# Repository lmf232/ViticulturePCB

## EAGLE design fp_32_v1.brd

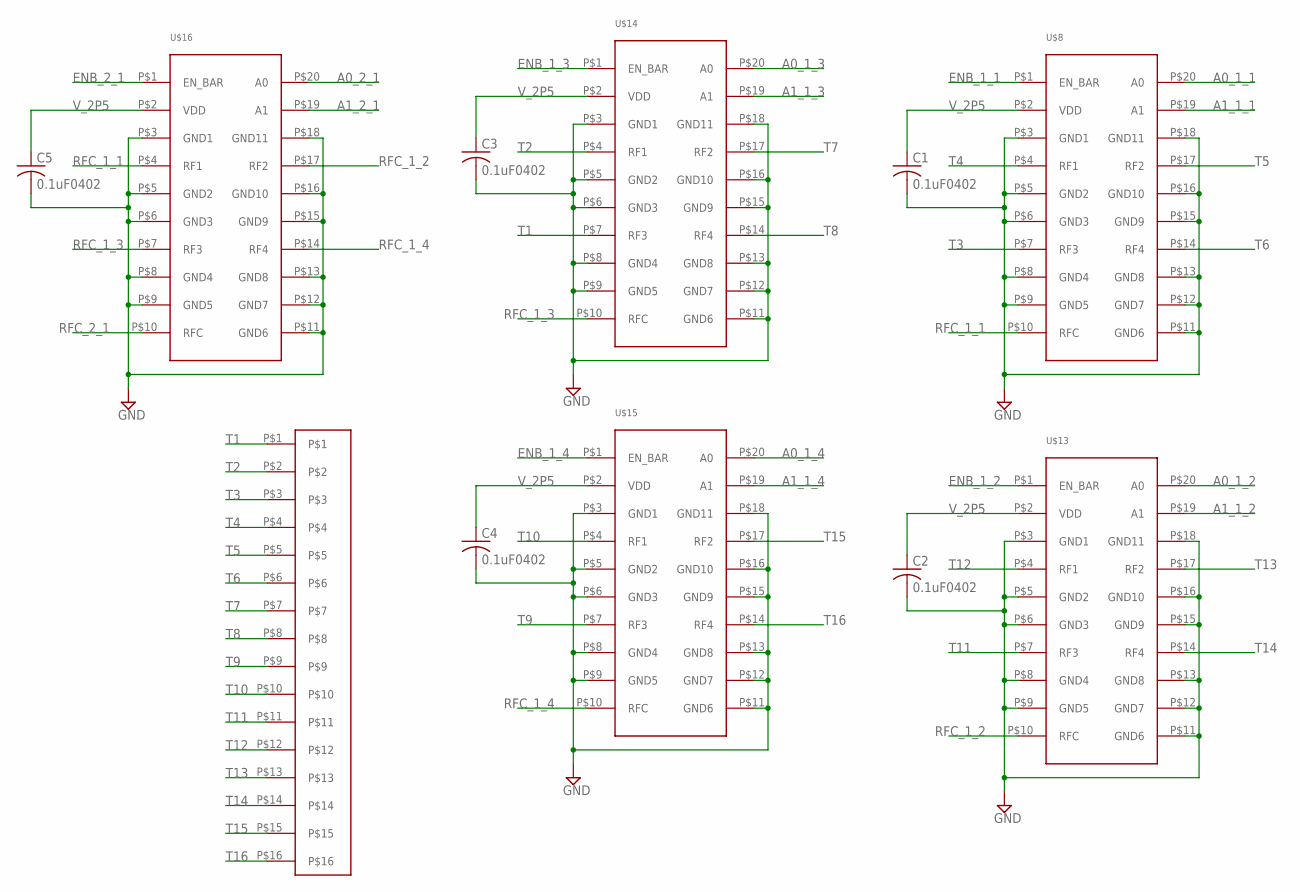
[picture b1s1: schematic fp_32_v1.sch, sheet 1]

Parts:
C1, C2, C3, C4, C5: 0.1uF0402; C0402
U$2: FP-BOND-6MIL; FP_BOND_6MIL
U$8, U$13, U$14, U$15, U$16: TICLIB2_ADG904; TICLIB2_ADG904_TSSOP

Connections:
A0_1_1: U$8.P$20 (A0); also elsewhere on the board
A0_1_2: U$13.P$20 (A0); also elsewhere on the board
A0_1_3: U$14.P$20 (A0); also elsewhere on the board
A0_1_4: U$15.P$20 (A0); also elsewhere on the board
A0_2_1: U$16.P$20 (A0); also elsewhere on the board
A1_1_1: U$8.P$19 (A1); also elsewhere on the board
A1_1_2: U$13.P$19 (A1); also elsewhere on the board
A1_1_3: U$14.P$19 (A1); also elsewhere on the board
A1_1_4: U$15.P$19 (A1); also elsewhere on the board
A1_2_1: U$16.P$19 (A1); also elsewhere on the board
ENB_1_1: U$8.P$1 (EN_BAR); also elsewhere on the board
ENB_1_2: U$13.P$1 (EN_BAR); also elsewhere on the board
ENB_1_3: U$14.P$1 (EN_BAR); also elsewhere on the board
ENB_1_4: U$15.P$1 (EN_BAR); also elsewhere on the board
ENB_2_1: U$16.P$1 (EN_BAR); also elsewhere on the board
GND: C1.2, C2.2, C3.2, C4.2, C5.2, U$8.P$3 (GND1), U$8.P$5 (GND2), U$8.P$6 (GND3), U$8.P$8 (GND4), U$8.P$9 (GND5), U$8.P$11 (GND6), U$8.P$12 (GND7), U$8.P$13 (GND8), U$8.P$15 (GND9), U$8.P$16 (GND10), U$8.P$18 (GND11), U$13.P$3 (GND1), U$13.P$5 (GND2), U$13.P$6 (GND3), U$13.P$8 (GND4), U$13.P$9 (GND5), U$13.P$11 (GND6), U$13.P$12 (GND7), U$13.P$13 (GND8), U$13.P$15 (GND9), U$13.P$16 (GND10), U$13.P$18 (GND11), U$14.P$3 (GND1), U$14.P$5 (GND2), U$14.P$6 (GND3), U$14.P$8 (GND4), U$14.P$9 (GND5), U$14.P$11 (GND6), U$14.P$12 (GND7), U$14.P$13 (GND8), U$14.P$15 (GND9), U$14.P$16 (GND10), U$14.P$18 (GND11), U$15.P$3 (GND1), U$15.P$5 (GND2), U$15.P$6 (GND3), U$15.P$8 (GND4), U$15.P$9 (GND5), U$15.P$11 (GND6), U$15.P$12 (GND7), U$15.P$13 (GND8), U$15.P$15 (GND9), U$15.P$16 (GND10), U$15.P$18 (GND11), U$16.P$3 (GND1), U$16.P$5 (GND2), U$16.P$6 (GND3), U$16.P$8 (GND4), U$16.P$9 (GND5), U$16.P$11 (GND6), U$16.P$12 (GND7), U$16.P$13 (GND8), U$16.P$15 (GND9), U$16.P$16 (GND10), U$16.P$18 (GND11); also elsewhere on the board
RFC_1_1: U$8.P$10 (RFC), U$16.P$4 (RF1)
RFC_1_2: U$13.P$10 (RFC), U$16.P$17 (RF2)
RFC_1_3: U$14.P$10 (RFC), U$16.P$7 (RF3)
RFC_1_4: U$15.P$10 (RFC), U$16.P$14 (RF4)
RFC_2_1: U$16.P$10 (RFC); also elsewhere on the board
T1: U$2.P$1, U$14.P$7 (RF3)
T2: U$2.P$2, U$14.P$4 (RF1)
T3: U$2.P$3, U$8.P$7 (RF3)
T4: U$2.P$4, U$8.P$4 (RF1)
T5: U$2.P$5, U$8.P$17 (RF2)
T6: U$2.P$6, U$8.P$14 (RF4)
T7: U$2.P$7, U$14.P$17 (RF2)
T8: U$2.P$8, U$14.P$14 (RF4)
T9: U$2.P$9, U$15.P$7 (RF3)
T10: U$2.P$10, U$15.P$4 (RF1)
T11: U$2.P$11, U$13.P$7 (RF3)
T12: U$2.P$12, U$13.P$4 (RF1)
T13: U$2.P$13, U$13.P$17 (RF2)
T14: U$2.P$14, U$13.P$14 (RF4)
T15: U$2.P$15, U$15.P$17 (RF2)
T16: U$2.P$16, U$15.P$14 (RF4)
V_2P5: C1.1, C2.1, C3.1, C4.1, C5.1, U$8.P$2 (VDD), U$13.P$2 (VDD), U$14.P$2 (VDD), U$15.P$2 (VDD), U$16.P$2 (VDD); also elsewhere on the board

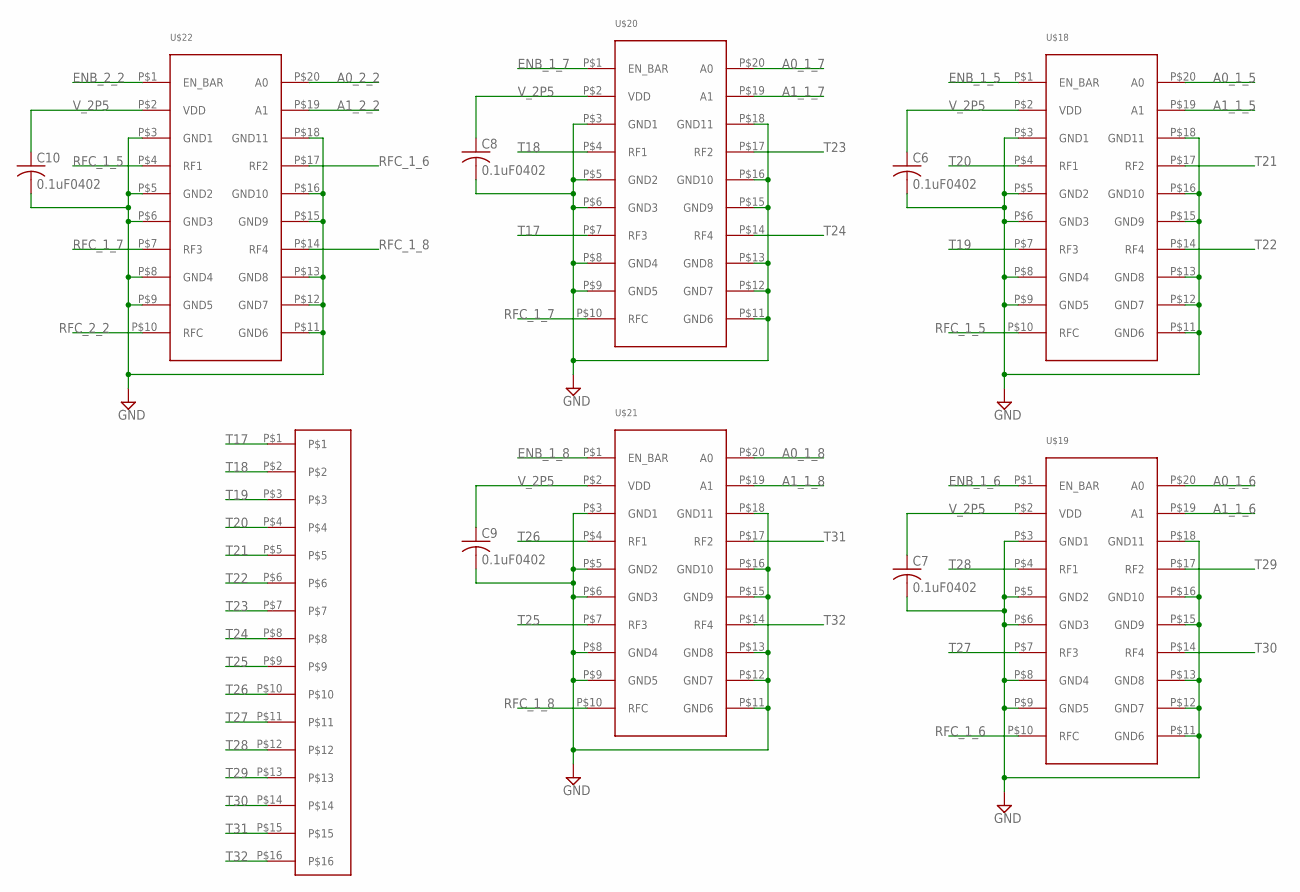
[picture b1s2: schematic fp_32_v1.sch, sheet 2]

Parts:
C6, C7, C8, C9, C10: 0.1uF0402; C0402
U$17: FP-BOND-6MIL; FP_BOND_6MIL
U$18, U$19, U$20, U$21, U$22: TICLIB2_ADG904; TICLIB2_ADG904_TSSOP

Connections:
A0_1_5: U$18.P$20 (A0); also elsewhere on the board
A0_1_6: U$19.P$20 (A0); also elsewhere on the board
A0_1_7: U$20.P$20 (A0); also elsewhere on the board
A0_1_8: U$21.P$20 (A0); also elsewhere on the board
A0_2_2: U$22.P$20 (A0); also elsewhere on the board
A1_1_5: U$18.P$19 (A1); also elsewhere on the board
A1_1_6: U$19.P$19 (A1); also elsewhere on the board
A1_1_7: U$20.P$19 (A1); also elsewhere on the board
A1_1_8: U$21.P$19 (A1); also elsewhere on the board
A1_2_2: U$22.P$19 (A1); also elsewhere on the board
ENB_1_5: U$18.P$1 (EN_BAR); also elsewhere on the board
ENB_1_6: U$19.P$1 (EN_BAR); also elsewhere on the board
ENB_1_7: U$20.P$1 (EN_BAR); also elsewhere on the board
ENB_1_8: U$21.P$1 (EN_BAR); also elsewhere on the board
ENB_2_2: U$22.P$1 (EN_BAR); also elsewhere on the board
GND: C6.2, C7.2, C8.2, C9.2, C10.2, U$18.P$3 (GND1), U$18.P$5 (GND2), U$18.P$6 (GND3), U$18.P$8 (GND4), U$18.P$9 (GND5), U$18.P$11 (GND6), U$18.P$12 (GND7), U$18.P$13 (GND8), U$18.P$15 (GND9), U$18.P$16 (GND10), U$18.P$18 (GND11), U$19.P$3 (GND1), U$19.P$5 (GND2), U$19.P$6 (GND3), U$19.P$8 (GND4), U$19.P$9 (GND5), U$19.P$11 (GND6), U$19.P$12 (GND7), U$19.P$13 (GND8), U$19.P$15 (GND9), U$19.P$16 (GND10), U$19.P$18 (GND11), U$20.P$3 (GND1), U$20.P$5 (GND2), U$20.P$6 (GND3), U$20.P$8 (GND4), U$20.P$9 (GND5), U$20.P$11 (GND6), U$20.P$12 (GND7), U$20.P$13 (GND8), U$20.P$15 (GND9), U$20.P$16 (GND10), U$20.P$18 (GND11), U$21.P$3 (GND1), U$21.P$5 (GND2), U$21.P$6 (GND3), U$21.P$8 (GND4), U$21.P$9 (GND5), U$21.P$11 (GND6), U$21.P$12 (GND7), U$21.P$13 (GND8), U$21.P$15 (GND9), U$21.P$16 (GND10), U$21.P$18 (GND11), U$22.P$3 (GND1), U$22.P$5 (GND2), U$22.P$6 (GND3), U$22.P$8 (GND4), U$22.P$9 (GND5), U$22.P$11 (GND6), U$22.P$12 (GND7), U$22.P$13 (GND8), U$22.P$15 (GND9), U$22.P$16 (GND10), U$22.P$18 (GND11); also elsewhere on the board
RFC_1_5: U$18.P$10 (RFC), U$22.P$4 (RF1)
RFC_1_6: U$19.P$10 (RFC), U$22.P$17 (RF2)
RFC_1_7: U$20.P$10 (RFC), U$22.P$7 (RF3)
RFC_1_8: U$21.P$10 (RFC), U$22.P$14 (RF4)
RFC_2_2: U$22.P$10 (RFC); also elsewhere on the board
T17: U$17.P$1, U$20.P$7 (RF3)
T18: U$17.P$2, U$20.P$4 (RF1)
T19: U$17.P$3, U$18.P$7 (RF3)
T20: U$17.P$4, U$18.P$4 (RF1)
T21: U$17.P$5, U$18.P$17 (RF2)
T22: U$17.P$6, U$18.P$14 (RF4)
T23: U$17.P$7, U$20.P$17 (RF2)
T24: U$17.P$8, U$20.P$14 (RF4)
T25: U$17.P$9, U$21.P$7 (RF3)
T26: U$17.P$10, U$21.P$4 (RF1)
T27: U$17.P$11, U$19.P$7 (RF3)
T28: U$17.P$12, U$19.P$4 (RF1)
T29: U$17.P$13, U$19.P$17 (RF2)
T30: U$17.P$14, U$19.P$14 (RF4)
T31: U$17.P$15, U$21.P$17 (RF2)
T32: U$17.P$16, U$21.P$14 (RF4)
V_2P5: C6.1, C7.1, C8.1, C9.1, C10.1, U$18.P$2 (VDD), U$19.P$2 (VDD), U$20.P$2 (VDD), U$21.P$2 (VDD), U$22.P$2 (VDD); also elsewhere on the board

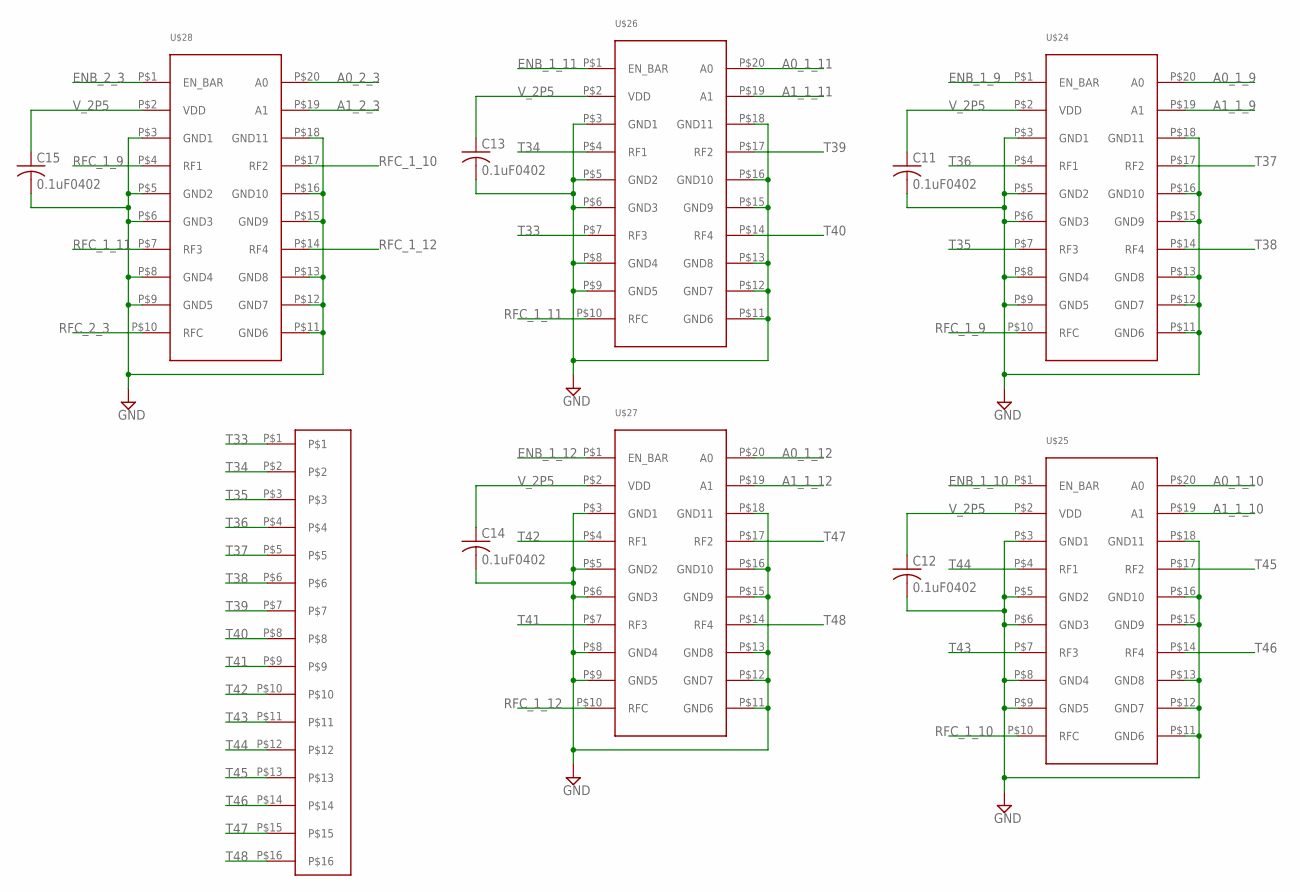
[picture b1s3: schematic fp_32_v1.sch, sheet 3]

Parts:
C11, C12, C13, C14, C15: 0.1uF0402; C0402
U$23: FP-BOND-6MIL; FP_BOND_6MIL
U$24, U$25, U$26, U$27, U$28: TICLIB2_ADG904; TICLIB2_ADG904_TSSOP

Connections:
A0_1_9: U$24.P$20 (A0); also elsewhere on the board
A0_1_10: U$25.P$20 (A0); also elsewhere on the board
A0_1_11: U$26.P$20 (A0); also elsewhere on the board
A0_1_12: U$27.P$20 (A0); also elsewhere on the board
A0_2_3: U$28.P$20 (A0); also elsewhere on the board
A1_1_9: U$24.P$19 (A1); also elsewhere on the board
A1_1_10: U$25.P$19 (A1); also elsewhere on the board
A1_1_11: U$26.P$19 (A1); also elsewhere on the board
A1_1_12: U$27.P$19 (A1); also elsewhere on the board
A1_2_3: U$28.P$19 (A1); also elsewhere on the board
ENB_1_9: U$24.P$1 (EN_BAR); also elsewhere on the board
ENB_1_10: U$25.P$1 (EN_BAR); also elsewhere on the board
ENB_1_11: U$26.P$1 (EN_BAR); also elsewhere on the board
ENB_1_12: U$27.P$1 (EN_BAR); also elsewhere on the board
ENB_2_3: U$28.P$1 (EN_BAR); also elsewhere on the board
GND: C11.2, C12.2, C13.2, C14.2, C15.2, U$24.P$3 (GND1), U$24.P$5 (GND2), U$24.P$6 (GND3), U$24.P$8 (GND4), U$24.P$9 (GND5), U$24.P$11 (GND6), U$24.P$12 (GND7), U$24.P$13 (GND8), U$24.P$15 (GND9), U$24.P$16 (GND10), U$24.P$18 (GND11), U$25.P$3 (GND1), U$25.P$5 (GND2), U$25.P$6 (GND3), U$25.P$8 (GND4), U$25.P$9 (GND5), U$25.P$11 (GND6), U$25.P$12 (GND7), U$25.P$13 (GND8), U$25.P$15 (GND9), U$25.P$16 (GND10), U$25.P$18 (GND11), U$26.P$3 (GND1), U$26.P$5 (GND2), U$26.P$6 (GND3), U$26.P$8 (GND4), U$26.P$9 (GND5), U$26.P$11 (GND6), U$26.P$12 (GND7), U$26.P$13 (GND8), U$26.P$15 (GND9), U$26.P$16 (GND10), U$26.P$18 (GND11), U$27.P$3 (GND1), U$27.P$5 (GND2), U$27.P$6 (GND3), U$27.P$8 (GND4), U$27.P$9 (GND5), U$27.P$11 (GND6), U$27.P$12 (GND7), U$27.P$13 (GND8), U$27.P$15 (GND9), U$27.P$16 (GND10), U$27.P$18 (GND11), U$28.P$3 (GND1), U$28.P$5 (GND2), U$28.P$6 (GND3), U$28.P$8 (GND4), U$28.P$9 (GND5), U$28.P$11 (GND6), U$28.P$12 (GND7), U$28.P$13 (GND8), U$28.P$15 (GND9), U$28.P$16 (GND10), U$28.P$18 (GND11); also elsewhere on the board
RFC_1_9: U$24.P$10 (RFC), U$28.P$4 (RF1)
RFC_1_10: U$25.P$10 (RFC), U$28.P$17 (RF2)
RFC_1_11: U$26.P$10 (RFC), U$28.P$7 (RF3)
RFC_1_12: U$27.P$10 (RFC), U$28.P$14 (RF4)
RFC_2_3: U$28.P$10 (RFC); also elsewhere on the board
T33: U$23.P$1, U$26.P$7 (RF3)
T34: U$23.P$2, U$26.P$4 (RF1)
T35: U$23.P$3, U$24.P$7 (RF3)
T36: U$23.P$4, U$24.P$4 (RF1)
T37: U$23.P$5, U$24.P$17 (RF2)
T38: U$23.P$6, U$24.P$14 (RF4)
T39: U$23.P$7, U$26.P$17 (RF2)
T40: U$23.P$8, U$26.P$14 (RF4)
T41: U$23.P$9, U$27.P$7 (RF3)
T42: U$23.P$10, U$27.P$4 (RF1)
T43: U$23.P$11, U$25.P$7 (RF3)
T44: U$23.P$12, U$25.P$4 (RF1)
T45: U$23.P$13, U$25.P$17 (RF2)
T46: U$23.P$14, U$25.P$14 (RF4)
T47: U$23.P$15, U$27.P$17 (RF2)
T48: U$23.P$16, U$27.P$14 (RF4)
V_2P5: C11.1, C12.1, C13.1, C14.1, C15.1, U$24.P$2 (VDD), U$25.P$2 (VDD), U$26.P$2 (VDD), U$27.P$2 (VDD), U$28.P$2 (VDD); also elsewhere on the board

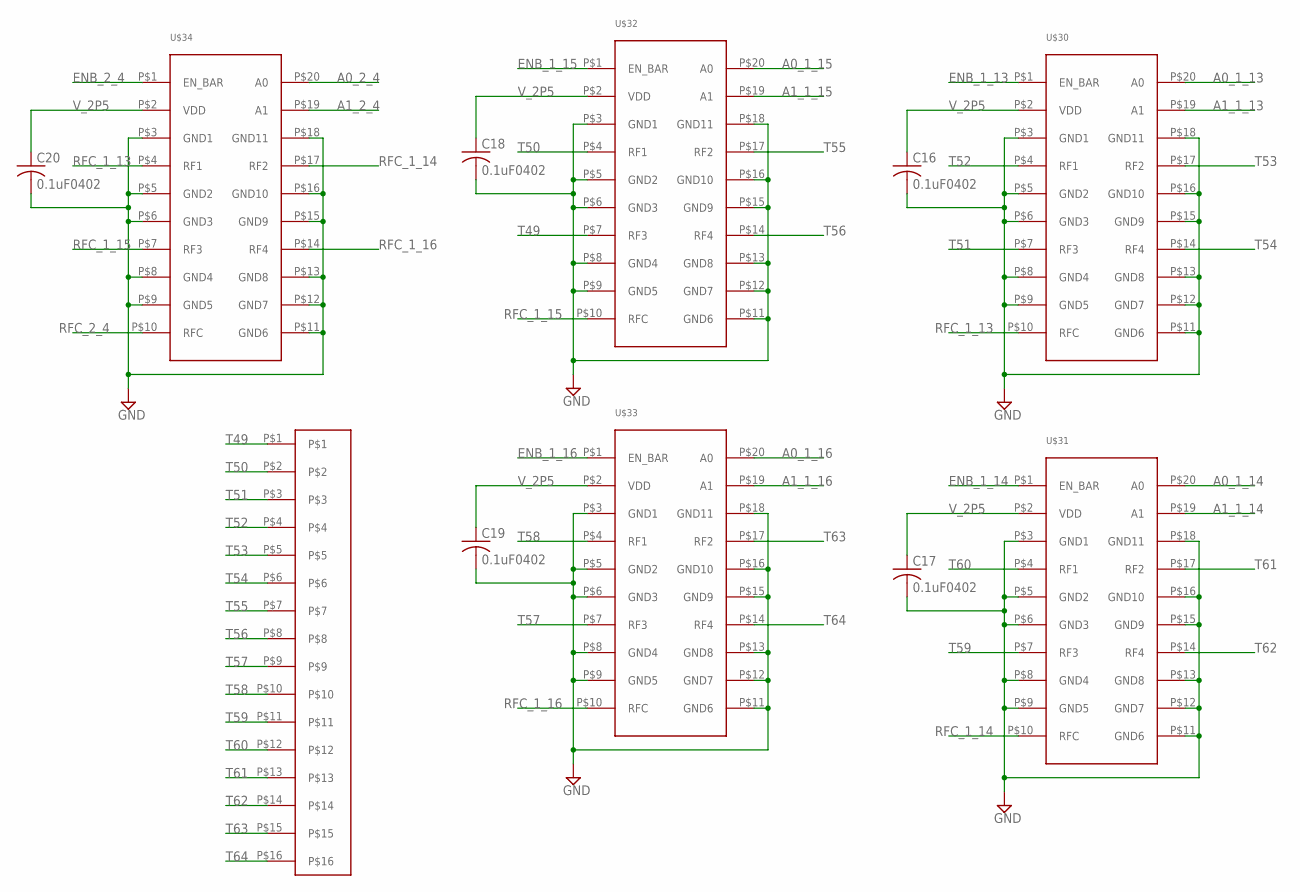
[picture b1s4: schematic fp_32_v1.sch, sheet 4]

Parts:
C16, C17, C18, C19, C20: 0.1uF0402; C0402
U$29: FP-BOND-6MIL; FP_BOND_6MIL
U$30, U$31, U$32, U$33, U$34: TICLIB2_ADG904; TICLIB2_ADG904_TSSOP

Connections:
A0_1_13: U$30.P$20 (A0); also elsewhere on the board
A0_1_14: U$31.P$20 (A0); also elsewhere on the board
A0_1_15: U$32.P$20 (A0); also elsewhere on the board
A0_1_16: U$33.P$20 (A0); also elsewhere on the board
A0_2_4: U$34.P$20 (A0); also elsewhere on the board
A1_1_13: U$30.P$19 (A1); also elsewhere on the board
A1_1_14: U$31.P$19 (A1); also elsewhere on the board
A1_1_15: U$32.P$19 (A1); also elsewhere on the board
A1_1_16: U$33.P$19 (A1); also elsewhere on the board
A1_2_4: U$34.P$19 (A1); also elsewhere on the board
ENB_1_13: U$30.P$1 (EN_BAR); also elsewhere on the board
ENB_1_14: U$31.P$1 (EN_BAR); also elsewhere on the board
ENB_1_15: U$32.P$1 (EN_BAR); also elsewhere on the board
ENB_1_16: U$33.P$1 (EN_BAR); also elsewhere on the board
ENB_2_4: U$34.P$1 (EN_BAR); also elsewhere on the board
GND: C16.2, C17.2, C18.2, C19.2, C20.2, U$30.P$3 (GND1), U$30.P$5 (GND2), U$30.P$6 (GND3), U$30.P$8 (GND4), U$30.P$9 (GND5), U$30.P$11 (GND6), U$30.P$12 (GND7), U$30.P$13 (GND8), U$30.P$15 (GND9), U$30.P$16 (GND10), U$30.P$18 (GND11), U$31.P$3 (GND1), U$31.P$5 (GND2), U$31.P$6 (GND3), U$31.P$8 (GND4), U$31.P$9 (GND5), U$31.P$11 (GND6), U$31.P$12 (GND7), U$31.P$13 (GND8), U$31.P$15 (GND9), U$31.P$16 (GND10), U$31.P$18 (GND11), U$32.P$3 (GND1), U$32.P$5 (GND2), U$32.P$6 (GND3), U$32.P$8 (GND4), U$32.P$9 (GND5), U$32.P$11 (GND6), U$32.P$12 (GND7), U$32.P$13 (GND8), U$32.P$15 (GND9), U$32.P$16 (GND10), U$32.P$18 (GND11), U$33.P$3 (GND1), U$33.P$5 (GND2), U$33.P$6 (GND3), U$33.P$8 (GND4), U$33.P$9 (GND5), U$33.P$11 (GND6), U$33.P$12 (GND7), U$33.P$13 (GND8), U$33.P$15 (GND9), U$33.P$16 (GND10), U$33.P$18 (GND11), U$34.P$3 (GND1), U$34.P$5 (GND2), U$34.P$6 (GND3), U$34.P$8 (GND4), U$34.P$9 (GND5), U$34.P$11 (GND6), U$34.P$12 (GND7), U$34.P$13 (GND8), U$34.P$15 (GND9), U$34.P$16 (GND10), U$34.P$18 (GND11); also elsewhere on the board
RFC_1_13: U$30.P$10 (RFC), U$34.P$4 (RF1)
RFC_1_14: U$31.P$10 (RFC), U$34.P$17 (RF2)
RFC_1_15: U$32.P$10 (RFC), U$34.P$7 (RF3)
RFC_1_16: U$33.P$10 (RFC), U$34.P$14 (RF4)
RFC_2_4: U$34.P$10 (RFC); also elsewhere on the board
T49: U$29.P$1, U$32.P$7 (RF3)
T50: U$29.P$2, U$32.P$4 (RF1)
T51: U$29.P$3, U$30.P$7 (RF3)
T52: U$29.P$4, U$30.P$4 (RF1)
T53: U$29.P$5, U$30.P$17 (RF2)
T54: U$29.P$6, U$30.P$14 (RF4)
T55: U$29.P$7, U$32.P$17 (RF2)
T56: U$29.P$8, U$32.P$14 (RF4)
T57: U$29.P$9, U$33.P$7 (RF3)
T58: U$29.P$10, U$33.P$4 (RF1)
T59: U$29.P$11, U$31.P$7 (RF3)
T60: U$29.P$12, U$31.P$4 (RF1)
T61: U$29.P$13, U$31.P$17 (RF2)
T62: U$29.P$14, U$31.P$14 (RF4)
T63: U$29.P$15, U$33.P$17 (RF2)
T64: U$29.P$16, U$33.P$14 (RF4)
V_2P5: C16.1, C17.1, C18.1, C19.1, C20.1, U$30.P$2 (VDD), U$31.P$2 (VDD), U$32.P$2 (VDD), U$33.P$2 (VDD), U$34.P$2 (VDD); also elsewhere on the board

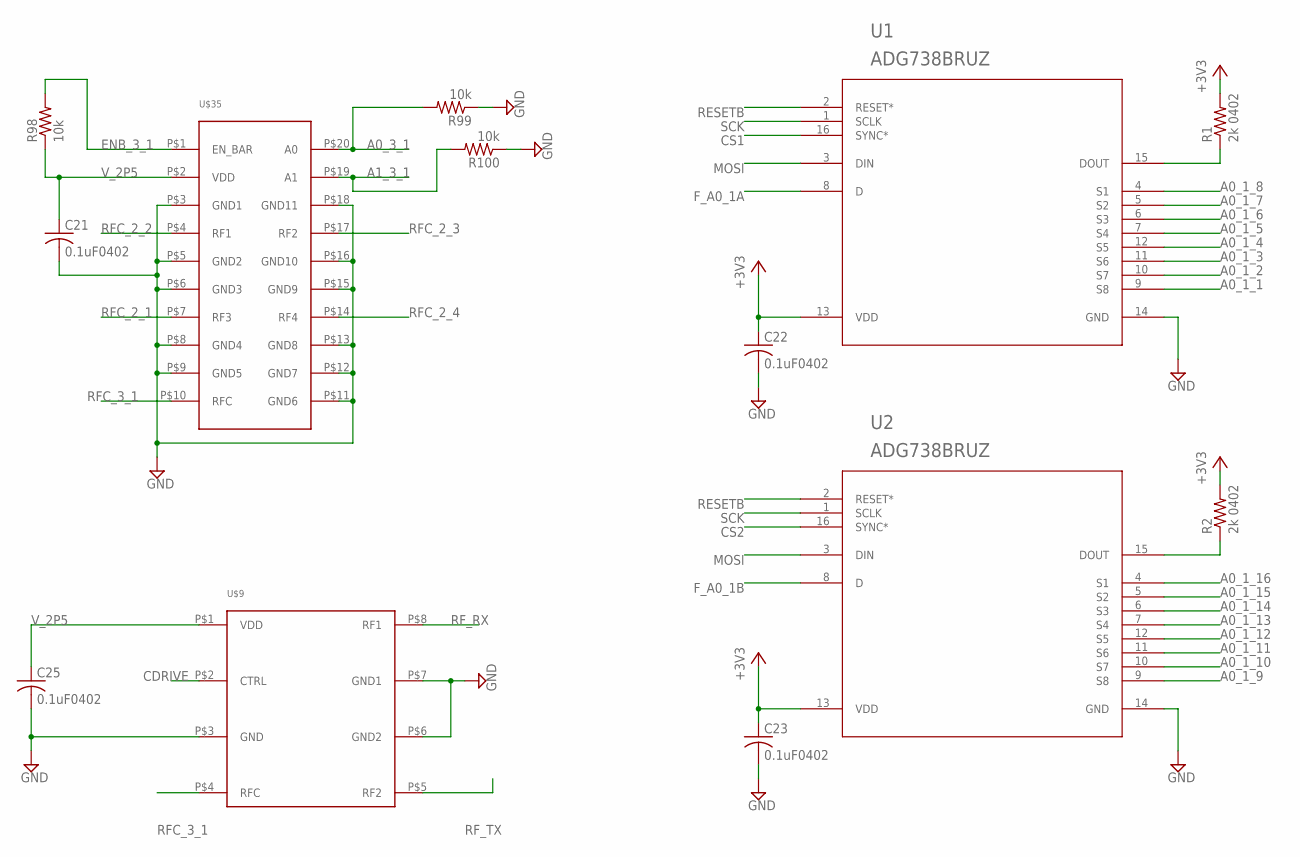
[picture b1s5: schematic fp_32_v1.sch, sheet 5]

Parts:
C21, C22, C23, C25: 0.1uF0402; C0402
R1, R2: 2k 0402; R0402
R98, R99, R100: 10k; R0402
U1, U2: ADG738BRUZ; RU_16
U$9: TIC_TESTING_ADG918BRMZ-500RL7CT; TIC_TESTING_ADG918BRMZ-500RL7CT-ND
U$35: TICLIB2_ADG904; TICLIB2_ADG904_TSSOP

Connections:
+3V3: C22.1, C23.1, R1.2, R2.2, U1.13 (VDD), U2.13 (VDD); also elsewhere on the board
A0_1_1: U1.9 (S8); also elsewhere on the board
A0_1_2: U1.10 (S7); also elsewhere on the board
A0_1_3: U1.11 (S6); also elsewhere on the board
A0_1_4: U1.12 (S5); also elsewhere on the board
A0_1_5: U1.7 (S4); also elsewhere on the board
A0_1_6: U1.6 (S3); also elsewhere on the board
A0_1_7: U1.5 (S2); also elsewhere on the board
A0_1_8: U1.4 (S1); also elsewhere on the board
A0_1_9: U2.9 (S8); also elsewhere on the board
A0_1_10: U2.10 (S7); also elsewhere on the board
A0_1_11: U2.11 (S6); also elsewhere on the board
A0_1_12: U2.12 (S5); also elsewhere on the board
A0_1_13: U2.7 (S4); also elsewhere on the board
A0_1_14: U2.6 (S3); also elsewhere on the board
A0_1_15: U2.5 (S2); also elsewhere on the board
A0_1_16: U2.4 (S1); also elsewhere on the board
A0_3_1: R99.2, U$35.P$20 (A0); also elsewhere on the board
A1_3_1: R100.2, U$35.P$19 (A1); also elsewhere on the board
CDRIVE: U$9.P$2 (CTRL); also elsewhere on the board
CS1: U1.16 (SYNC*); also elsewhere on the board
CS2: U2.16 (SYNC*); also elsewhere on the board
ENB_3_1: R98.2, U$35.P$1 (EN_BAR); also elsewhere on the board
F_A0_1A: U1.8 (D); also elsewhere on the board
F_A0_1B: U2.8 (D); also elsewhere on the board
GND: C21.2, C22.2, C23.2, C25.2, R99.1, R100.1, U1.14 (GND), U2.14 (GND), U$9.P$3 (GND), U$9.P$6 (GND2), U$9.P$7 (GND1), U$35.P$3 (GND1), U$35.P$5 (GND2), U$35.P$6 (GND3), U$35.P$8 (GND4), U$35.P$9 (GND5), U$35.P$11 (GND6), U$35.P$12 (GND7), U$35.P$13 (GND8), U$35.P$15 (GND9), U$35.P$16 (GND10), U$35.P$18 (GND11); also elsewhere on the board
MOSI: U1.3 (DIN), U2.3 (DIN); also elsewhere on the board
unnamed: R1.1, U1.15 (DOUT)
unnamed: R2.1, U2.15 (DOUT)
RESETB: U1.2 (RESET*), U2.2 (RESET*); also elsewhere on the board
RFC_2_1: U$35.P$7 (RF3); also elsewhere on the board
RFC_2_2: U$35.P$4 (RF1); also elsewhere on the board
RFC_2_3: U$35.P$17 (RF2); also elsewhere on the board
RFC_2_4: U$35.P$14 (RF4); also elsewhere on the board
RFC_3_1: U$9.P$4 (RFC), U$35.P$10 (RFC)
RF_RX: U$9.P$8 (RF1); also elsewhere on the board
RF_TX: U$9.P$5 (RF2); also elsewhere on the board
SCK: U1.1 (SCLK), U2.1 (SCLK); also elsewhere on the board
V_2P5: C21.1, C25.1, R98.1, U$9.P$1 (VDD), U$35.P$2 (VDD); also elsewhere on the board

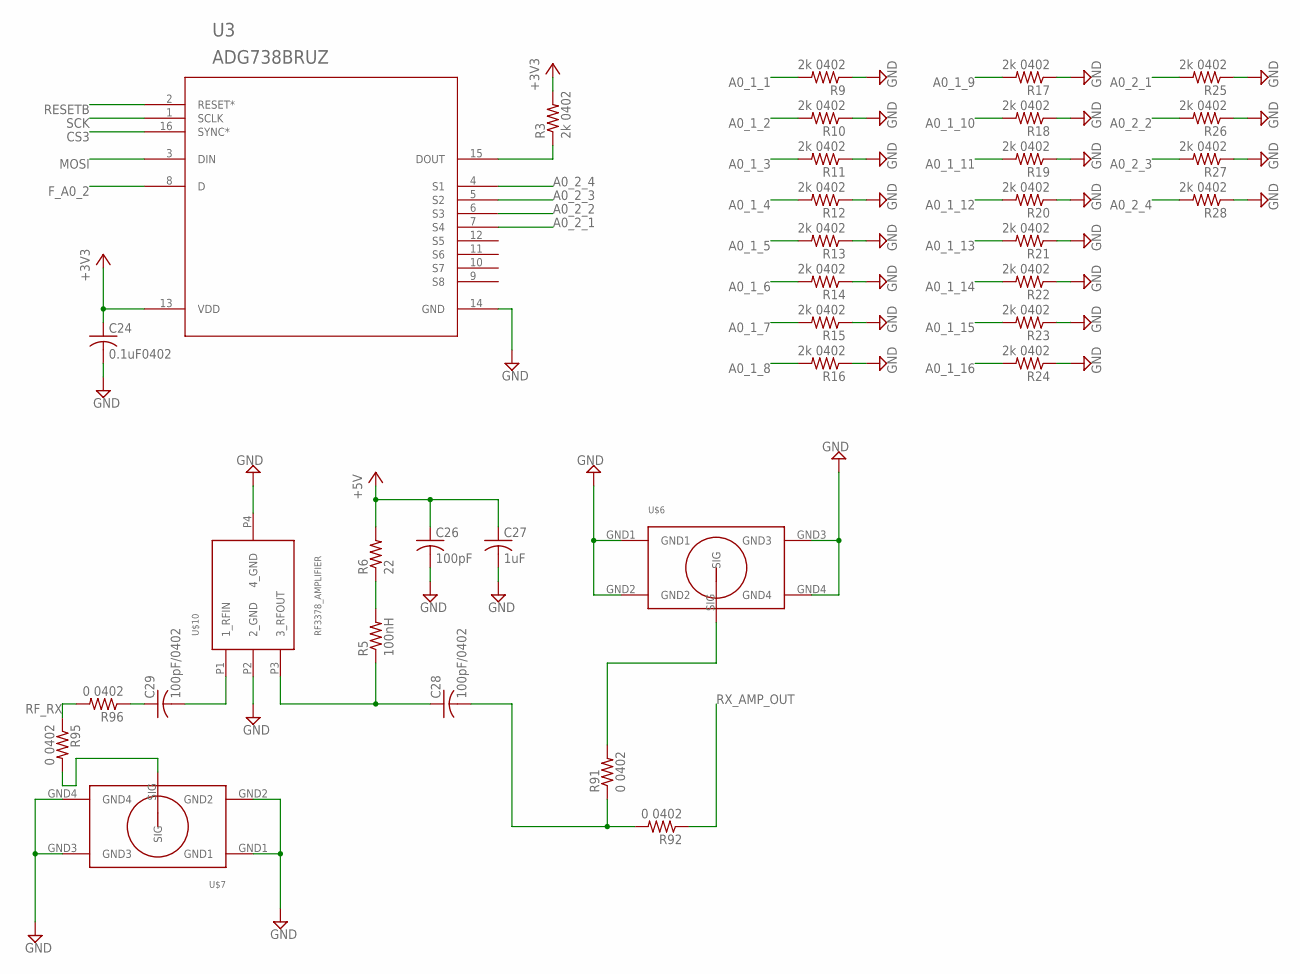
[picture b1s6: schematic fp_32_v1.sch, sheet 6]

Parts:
C24: 0.1uF0402; C0402
C26: 100pF; C0603
C27: 1uF; C0603
C28, C29: 100pF/0402; C0402
R3, R9, R10, R11, R12, R13, R14, R15, R16, R17, R18, R19, R20, R21, R22, R23, R24, R25, R26, R27, R28: 2k 0402; R0402
R5: 100nH; R0603
R6: 22; R0805
R91, R92, R95, R96: 0 0402; R0402
U3: ADG738BRUZ; RU_16
U$6, U$7: MINISMP_PE44970_THRUHOLE; MINISMP_PE44970_THRU_HOLE
U$10: RF3378_AMPLIFIER; TO243AA/SOT89

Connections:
+3V3: C24.1, R3.2, U3.13 (VDD); also elsewhere on the board
+5V: C26.1, C27.1, R6.2; also elsewhere on the board
A0_1_1: R9.2; also elsewhere on the board
A0_1_2: R10.2; also elsewhere on the board
A0_1_3: R11.2; also elsewhere on the board
A0_1_4: R12.2; also elsewhere on the board
A0_1_5: R13.2; also elsewhere on the board
A0_1_6: R14.2; also elsewhere on the board
A0_1_7: R15.2; also elsewhere on the board
A0_1_8: R16.2; also elsewhere on the board
A0_1_9: R17.2; also elsewhere on the board
A0_1_10: R18.2; also elsewhere on the board
A0_1_11: R19.2; also elsewhere on the board
A0_1_12: R20.2; also elsewhere on the board
A0_1_13: R21.2; also elsewhere on the board
A0_1_14: R22.2; also elsewhere on the board
A0_1_15: R23.2; also elsewhere on the board
A0_1_16: R24.2; also elsewhere on the board
A0_2_1: R25.2, U3.7 (S4); also elsewhere on the board
A0_2_2: R26.2, U3.6 (S3); also elsewhere on the board
A0_2_3: R27.2, U3.5 (S2); also elsewhere on the board
A0_2_4: R28.2, U3.4 (S1); also elsewhere on the board
CS3: U3.16 (SYNC*); also elsewhere on the board
F_A0_2: U3.8 (D); also elsewhere on the board
GND: C24.2, C26.2, C27.2, R9.1, R10.1, R11.1, R12.1, R13.1, R14.1, R15.1, R16.1, R17.1, R18.1, R19.1, R20.1, R21.1, R22.1, R23.1, R24.1, R25.1, R26.1, R27.1, R28.1, U3.14 (GND), U$6.GND1, U$6.GND2, U$6.GND3, U$6.GND4, U$7.GND1, U$7.GND2, U$7.GND3, U$7.GND4, U$10.P2 (2_GND), U$10.P4 (4_GND); also elsewhere on the board
MOSI: U3.3 (DIN); also elsewhere on the board
unnamed: R3.1, U3.15 (DOUT)
unnamed: C28.1, R5.1, U$10.P3 (3_RFOUT)
unnamed: R5.2, R6.1
unnamed: C29.2, U$10.P1 (1_RFIN)
unnamed: C28.2, R91.1, R92.2
unnamed: R91.2, U$6.SIG
unnamed: R95.2, U$7.SIG
unnamed: C29.1, R96.1
RESETB: U3.2 (RESET*); also elsewhere on the board
RF_RX: R95.1, R96.2; also elsewhere on the board
RX_AMP_OUT: R92.1; also elsewhere on the board
SCK: U3.1 (SCLK); also elsewhere on the board

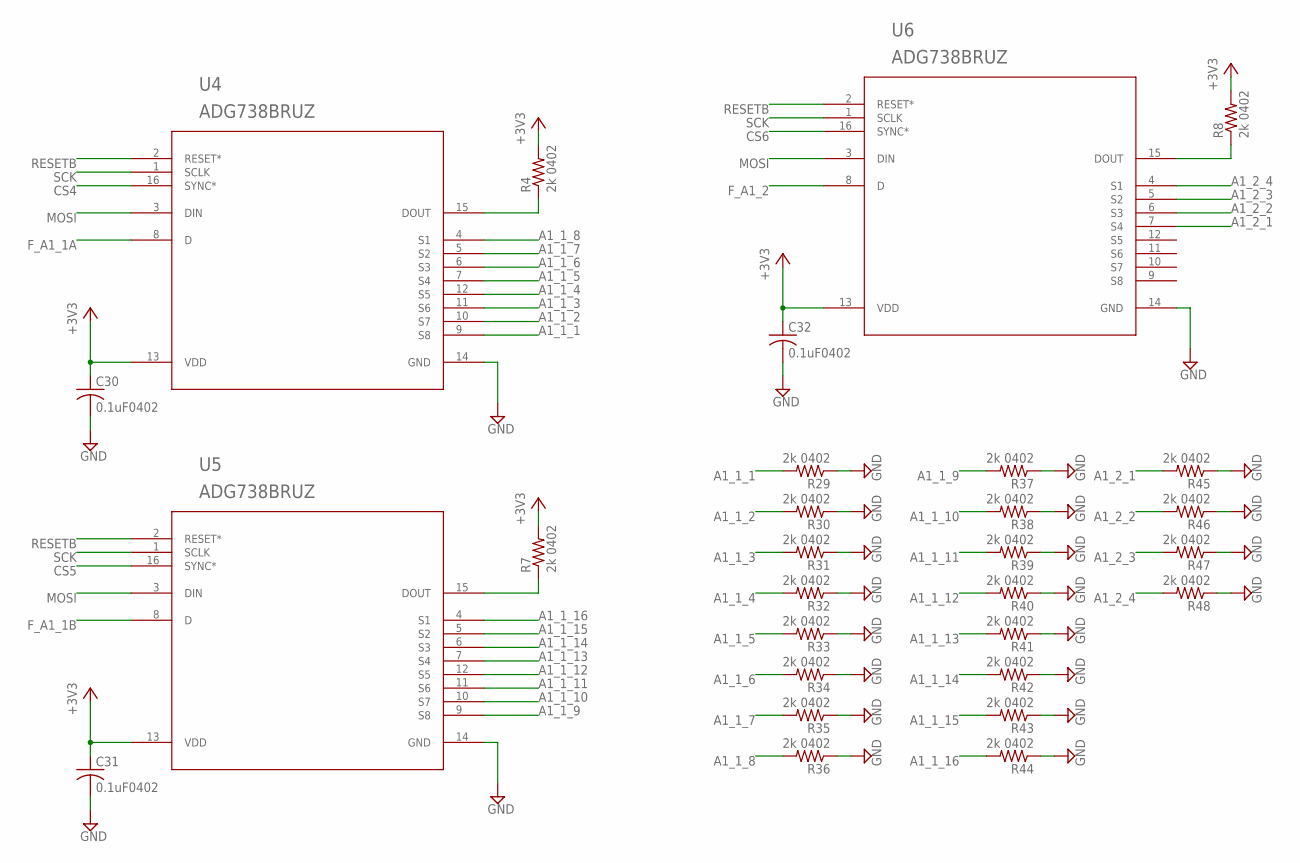
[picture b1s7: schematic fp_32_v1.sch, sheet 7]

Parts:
C30, C31, C32: 0.1uF0402; C0402
R4, R7, R8, R29, R30, R31, R32, R33, R34, R35, R36, R37, R38, R39, R40, R41, R42, R43, R44, R45, R46, R47, R48: 2k 0402; R0402
U4, U5, U6: ADG738BRUZ; RU_16

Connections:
+3V3: C30.1, C31.1, C32.1, R4.2, R7.2, R8.2, U4.13 (VDD), U5.13 (VDD), U6.13 (VDD); also elsewhere on the board
A1_1_1: R29.2, U4.9 (S8); also elsewhere on the board
A1_1_2: R30.2, U4.10 (S7); also elsewhere on the board
A1_1_3: R31.2, U4.11 (S6); also elsewhere on the board
A1_1_4: R32.2, U4.12 (S5); also elsewhere on the board
A1_1_5: R33.2, U4.7 (S4); also elsewhere on the board
A1_1_6: R34.2, U4.6 (S3); also elsewhere on the board
A1_1_7: R35.2, U4.5 (S2); also elsewhere on the board
A1_1_8: R36.2, U4.4 (S1); also elsewhere on the board
A1_1_9: R37.2, U5.9 (S8); also elsewhere on the board
A1_1_10: R38.2, U5.10 (S7); also elsewhere on the board
A1_1_11: R39.2, U5.11 (S6); also elsewhere on the board
A1_1_12: R40.2, U5.12 (S5); also elsewhere on the board
A1_1_13: R41.2, U5.7 (S4); also elsewhere on the board
A1_1_14: R42.2, U5.6 (S3); also elsewhere on the board
A1_1_15: R43.2, U5.5 (S2); also elsewhere on the board
A1_1_16: R44.2, U5.4 (S1); also elsewhere on the board
A1_2_1: R45.2, U6.7 (S4); also elsewhere on the board
A1_2_2: R46.2, U6.6 (S3); also elsewhere on the board
A1_2_3: R47.2, U6.5 (S2); also elsewhere on the board
A1_2_4: R48.2, U6.4 (S1); also elsewhere on the board
CS4: U4.16 (SYNC*); also elsewhere on the board
CS5: U5.16 (SYNC*); also elsewhere on the board
CS6: U6.16 (SYNC*); also elsewhere on the board
F_A1_1A: U4.8 (D); also elsewhere on the board
F_A1_1B: U5.8 (D); also elsewhere on the board
F_A1_2: U6.8 (D); also elsewhere on the board
GND: C30.2, C31.2, C32.2, R29.1, R30.1, R31.1, R32.1, R33.1, R34.1, R35.1, R36.1, R37.1, R38.1, R39.1, R40.1, R41.1, R42.1, R43.1, R44.1, R45.1, R46.1, R47.1, R48.1, U4.14 (GND), U5.14 (GND), U6.14 (GND); also elsewhere on the board
MOSI: U4.3 (DIN), U5.3 (DIN), U6.3 (DIN); also elsewhere on the board
unnamed: R4.1, U4.15 (DOUT)
unnamed: R7.1, U5.15 (DOUT)
unnamed: R8.1, U6.15 (DOUT)
RESETB: U4.2 (RESET*), U5.2 (RESET*), U6.2 (RESET*); also elsewhere on the board
SCK: U4.1 (SCLK), U5.1 (SCLK), U6.1 (SCLK); also elsewhere on the board

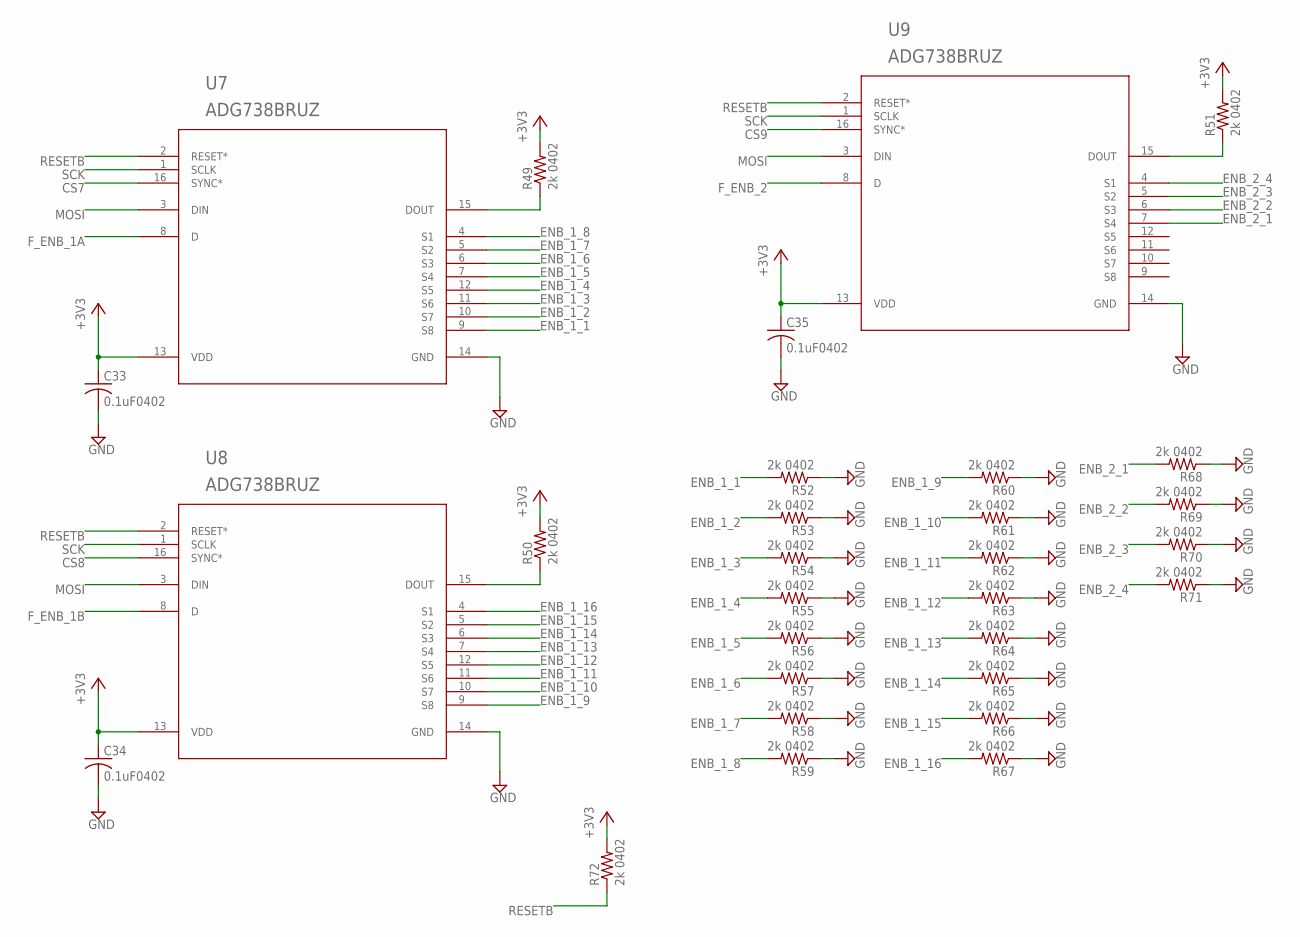
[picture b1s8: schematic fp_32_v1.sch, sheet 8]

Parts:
C33, C34, C35: 0.1uF0402; C0402
R49, R50, R51, R52, R53, R54, R55, R56, R57, R58, R59, R60, R61, R62, R63, R64, R65, R66, R67, R68, R69, R70, R71, R72: 2k 0402; R0402
U7, U8, U9: ADG738BRUZ; RU_16

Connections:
+3V3: C33.1, C34.1, C35.1, R49.2, R50.2, R51.2, R72.2, U7.13 (VDD), U8.13 (VDD), U9.13 (VDD); also elsewhere on the board
CS7: U7.16 (SYNC*); also elsewhere on the board
CS8: U8.16 (SYNC*); also elsewhere on the board
CS9: U9.16 (SYNC*); also elsewhere on the board
ENB_1_1: R52.2, U7.9 (S8); also elsewhere on the board
ENB_1_2: R53.2, U7.10 (S7); also elsewhere on the board
ENB_1_3: R54.2, U7.11 (S6); also elsewhere on the board
ENB_1_4: R55.2, U7.12 (S5); also elsewhere on the board
ENB_1_5: R56.2, U7.7 (S4); also elsewhere on the board
ENB_1_6: R57.2, U7.6 (S3); also elsewhere on the board
ENB_1_7: R58.2, U7.5 (S2); also elsewhere on the board
ENB_1_8: R59.2, U7.4 (S1); also elsewhere on the board
ENB_1_9: R60.2, U8.9 (S8); also elsewhere on the board
ENB_1_10: R61.2, U8.10 (S7); also elsewhere on the board
ENB_1_11: R62.2, U8.11 (S6); also elsewhere on the board
ENB_1_12: R63.2, U8.12 (S5); also elsewhere on the board
ENB_1_13: R64.2, U8.7 (S4); also elsewhere on the board
ENB_1_14: R65.2, U8.6 (S3); also elsewhere on the board
ENB_1_15: R66.2, U8.5 (S2); also elsewhere on the board
ENB_1_16: R67.2, U8.4 (S1); also elsewhere on the board
ENB_2_1: R68.2, U9.7 (S4); also elsewhere on the board
ENB_2_2: R69.2, U9.6 (S3); also elsewhere on the board
ENB_2_3: R70.2, U9.5 (S2); also elsewhere on the board
ENB_2_4: R71.2, U9.4 (S1); also elsewhere on the board
F_ENB_1A: U7.8 (D); also elsewhere on the board
F_ENB_1B: U8.8 (D); also elsewhere on the board
F_ENB_2: U9.8 (D); also elsewhere on the board
GND: C33.2, C34.2, C35.2, R52.1, R53.1, R54.1, R55.1, R56.1, R57.1, R58.1, R59.1, R60.1, R61.1, R62.1, R63.1, R64.1, R65.1, R66.1, R67.1, R68.1, R69.1, R70.1, R71.1, U7.14 (GND), U8.14 (GND), U9.14 (GND); also elsewhere on the board
MOSI: U7.3 (DIN), U8.3 (DIN), U9.3 (DIN); also elsewhere on the board
unnamed: R49.1, U7.15 (DOUT)
unnamed: R50.1, U8.15 (DOUT)
unnamed: R51.1, U9.15 (DOUT)
RESETB: R72.1, U7.2 (RESET*), U8.2 (RESET*), U9.2 (RESET*); also elsewhere on the board
SCK: U7.1 (SCLK), U8.1 (SCLK), U9.1 (SCLK); also elsewhere on the board

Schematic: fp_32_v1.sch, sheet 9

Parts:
C36, C37, C38: 100nF; C0603
C39: 0.1uF; C0603
C40: 0.01uF; C0603
R73: 10k; R0603
R74, R75, R76, R77, R80, R81: 0; R0603
R78: 50; R0603
U$36: RF_SWITCH_SPDT_HMC547LP3; CP_16_3
U$37: ZENER_MMSZ4689-TP; SOD123
U$44: FAIRCHILD_UHS_DUAL_INVERTER_NC7WZ04P6X; FAIRCHILD_DUAL_INVERTER_NC7WZ04P6X

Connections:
-5V: C39.2, C40.2, R73.2, U$44.2 (GND); also elsewhere on the board
GND: C39.1, C40.1, R78.2, U$36.1 (1_NC), U$36.2 (2_GND), U$36.4 (4_GND), U$36.5 (5_NC), U$36.6 (6_GND), U$36.8 (8_GND), U$36.9 (9_NC), U$36.12 (12_NC), U$36.13 (13_GND), U$36.15 (15_GND), U$36.16 (16_NC), U$36.17 (EP), U$44.5 (VCC); also elsewhere on the board
unnamed: C36.2, U$36.3 (3_RFC)
unnamed: C38.1, R78.1
unnamed: C37.2, U$36.7 (7_RF1)
unnamed: C38.2, U$36.14 (14_RF2)
unnamed: R80.2, U$36.11 (11_A)
unnamed: R76.1, R77.1, R81.1
unnamed: R73.1, U$37.A, U$44.1 (A1)
unnamed: R81.2, U$36.10 (10_B)
unnamed: R74.1, R75.1, R80.1
RF_SOURCE: C36.1; also elsewhere on the board
SX_CTRL_1P: R74.2, R76.2, U$44.4 (Y2)
SX_CTRL_N: R75.2, R77.2, U$44.3 (A2), U$44.6 (Y1)
TX_PULSE: U$37.C; also elsewhere on the board
TX_SWITCH_OUT: C37.1; also elsewhere on the board

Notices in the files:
parts and their libraries:
SparkFun: Licensing: CC v3.0 Share-Alike You are welcome to use this library for commercial purposes.
